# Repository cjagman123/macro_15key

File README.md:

# macro_15key
PCB Design for 15 Key LED Macro Keyboard

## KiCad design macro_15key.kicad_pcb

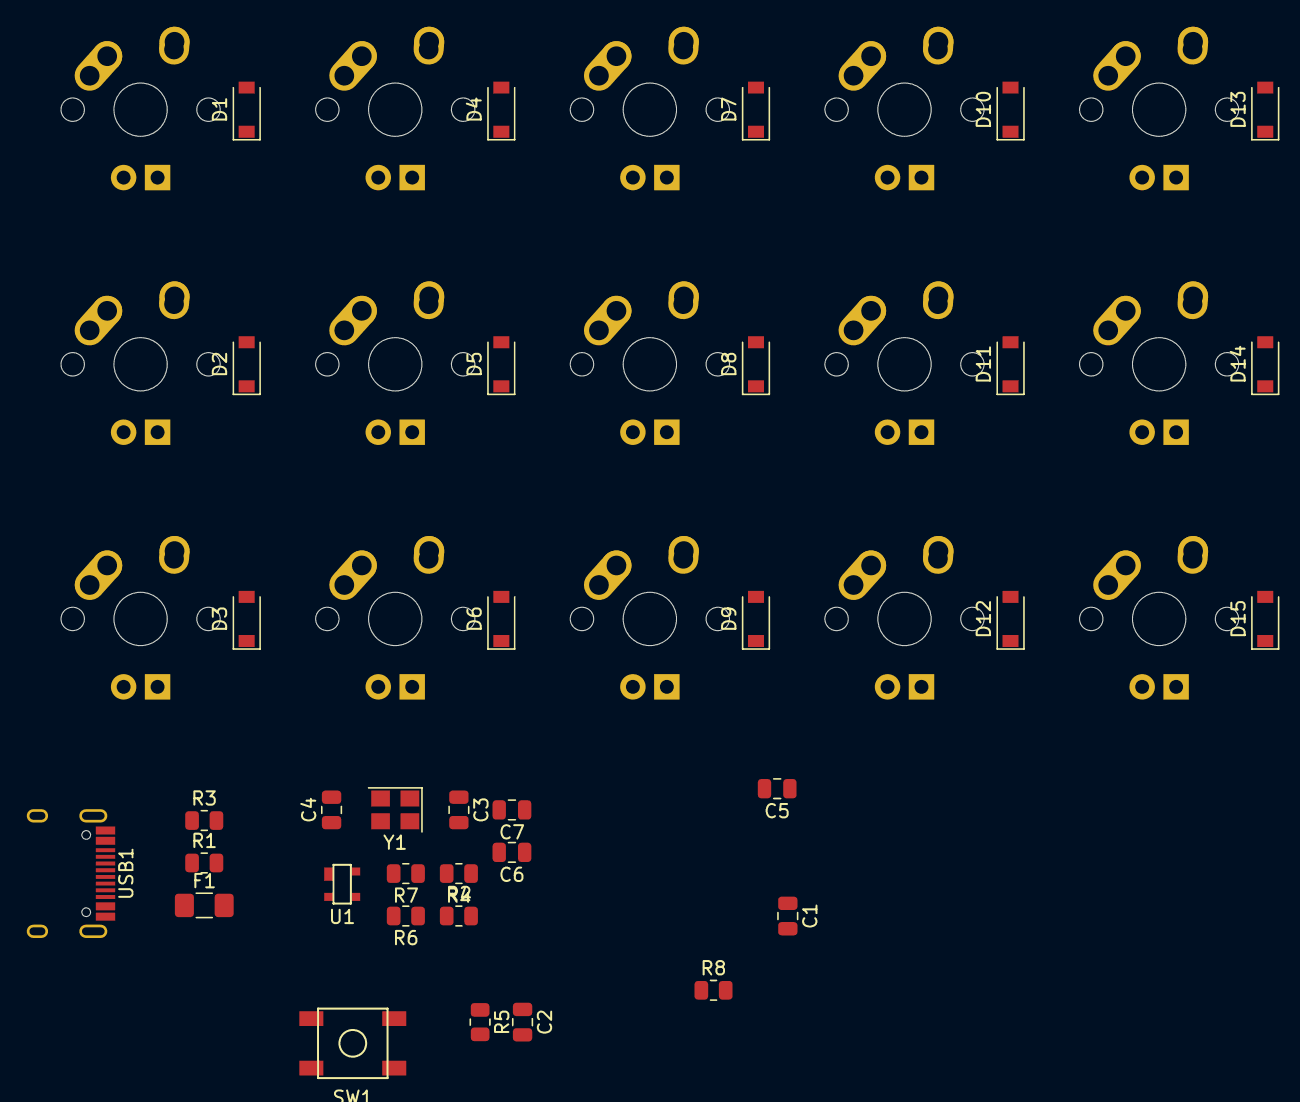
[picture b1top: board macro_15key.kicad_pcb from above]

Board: 2 copper layers, 51 parts (1 on the bottom side), 39 nets, no tracks yet.

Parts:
C1, C2, C5: 0.1uF; C_0805_2012Metric
C3, C4: 22pF; C_0805_2012Metric
C6: 1uF; C_0805_2012Metric
C7: 10uF; C_0805_2012Metric
D1, D2, D3, D4, D5, D6, D7, D8, D9, D10, D11, D12, D13, D14, D15: SOD-123; D_SOD-123
F1: 500m; Fuse_1206_3216Metric_Pad1.42x1.75mm_HandSolder
MX1, MX2, MX3, MX4, MX5, MX6, MX7, MX8, MX9, MX10, MX11, MX12, MX13, MX14, MX15: MX-LED; MX-1U
R1, R3: 5.1k; R_0805_2012Metric
R2, R4, R6, R7: 22; R_0805_2012Metric
R5, R8: 10k; R_0805_2012Metric
SW1: SW_Push; SKQG-1155865
U1: PRTR5V0U2X; SOT143B
U2: ATmega32U4-AU; TQFP-44_10x10mm_P0.8mm
USB1: HRO-TYPE-C-31-M-12
Y1: 16MHz; Crystal_SMD_3225-4Pin_3.2x2.5mm

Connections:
+5V: C1.1, C2.1, C5.1, C7.1, F1.1, R5.1, U2.2, U2.7, U2.14, U2.24, U2.34, U2.44
COL0: MX1.1, MX2.1, MX3.1, U2.11
COL1: MX4.1, MX5.1, MX6.1, U2.28
COL2: MX7.1, MX8.1, MX9.1, U2.29
COL3: MX10.1, MX11.1, MX12.1, U2.30
COL4: MX13.1, MX14.1, MX15.1, U2.12
D+: R4.2, R7.1
D-: R2.2, R6.1
GND: C1.2, C2.2, C3.2, C4.2, C5.2, C6.2, C7.2, R1.2, R3.2, R8.1, SW1.1, U1.1, U2.5, U2.15, U2.23, U2.35, U2.43, USB1.1, USB1.12, USB1.13, Y1.2, Y1.4
unnamed: C3.1, U2.17, Y1.1
unnamed: C4.1, U2.16, Y1.3
unnamed: C6.1, U2.6
unnamed: D1.2, MX1.2
unnamed: D2.2, MX2.2
unnamed: D3.2, MX3.2
unnamed: D4.2, MX4.2
unnamed: D5.2, MX5.2
unnamed: D6.2, MX6.2
unnamed: D7.2, MX7.2
unnamed: D8.2, MX8.2
unnamed: D9.2, MX9.2
unnamed: D10.2, MX10.2
unnamed: D11.2, MX11.2
unnamed: D12.2, MX12.2
unnamed: D13.2, MX13.2
unnamed: D14.2, MX14.2
unnamed: D15.2, MX15.2
unnamed: R1.1, USB1.10
unnamed: R2.1, U2.3
unnamed: R3.1, USB1.4
unnamed: R4.1, U2.4
unnamed: R5.2, SW1.2, U2.13
unnamed: R6.2, U1.3, USB1.5, USB1.7
unnamed: R7.2, U1.2, USB1.6, USB1.8
unnamed: R8.2, U2.33
ROW0: D1.1, D4.1, D7.1, D10.1, D13.1, U2.8
ROW1: D2.1, D5.1, D8.1, D11.1, D14.1, U2.9
ROW2: D3.1, D6.1, D9.1, D12.1, D15.1, U2.10
VCC: F1.2, U1.4, USB1.2, USB1.11

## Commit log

2020-10-11 Initial cad files
2020-10-11 Adding Mx and random parts Submodules
2020-10-11 adding fp and sym files
2020-10-13 adding type c library
2020-10-14 initial layout of pcb complete
